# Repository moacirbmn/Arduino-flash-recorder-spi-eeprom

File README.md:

# Arduino-flash-recorder-spi-eeprom

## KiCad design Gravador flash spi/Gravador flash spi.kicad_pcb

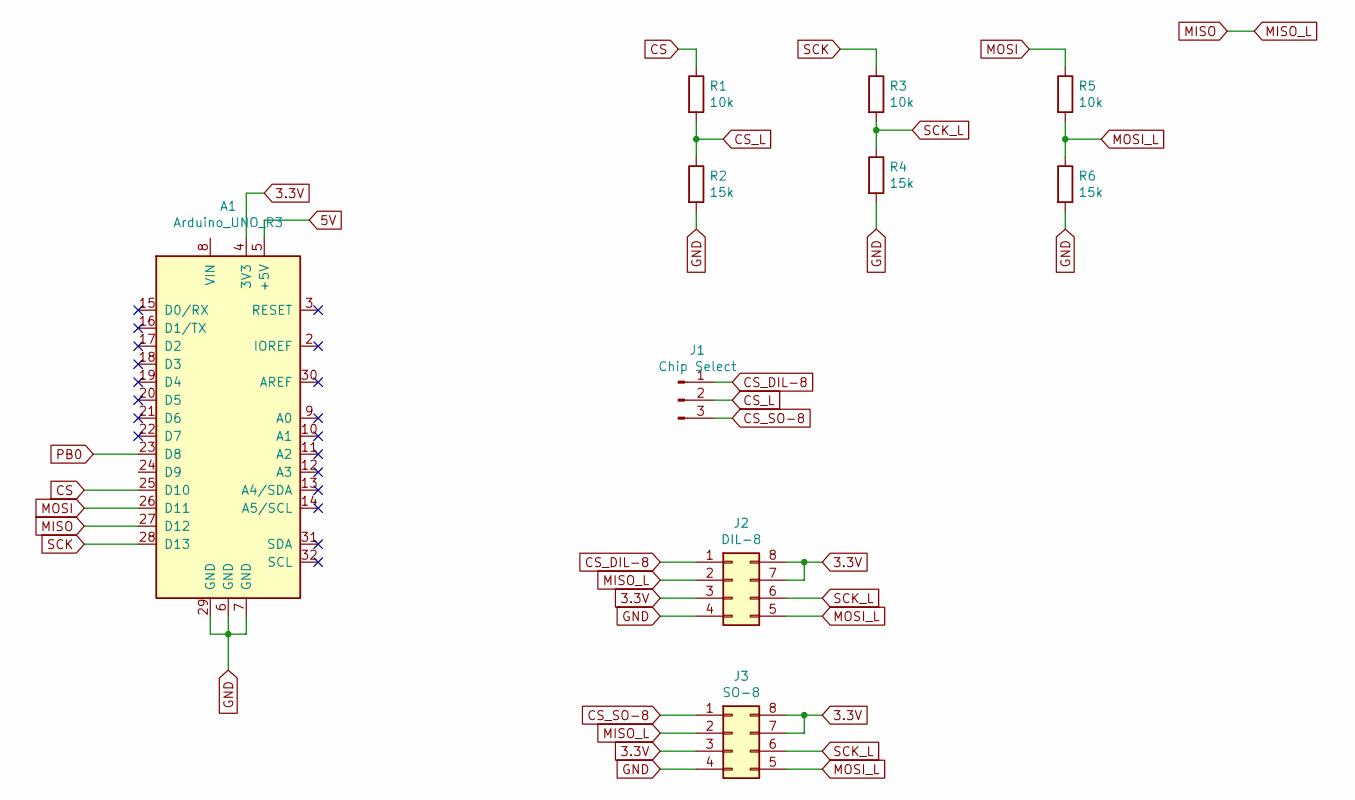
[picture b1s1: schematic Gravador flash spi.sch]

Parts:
A1: Arduino_UNO_R3; Arduino_UNO_R3_WithMountingHoles
J1: Chip Select; Pin_Header_Straight_1x03_Pitch2.54mm
J2: DIL-8; DIP-8_W7.62mm_LongPads
J3: SO-8; SO-8_5.3x6.2mm_Pitch1.27mm
R1, R3, R5: 10k; R_0805
R2, R4, R6: 15k; R_0805

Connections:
3.3V: A1.4 (3V3), J2.3, J2.7, J2.8, J3.3, J3.7, J3.8
5V: A1.5 (+5V)
CS: A1.25 (D10), R1.1
CS_DIL-8: J1.1, J2.1
CS_L: J1.2, R1.2, R2.1
CS_SO-8: J1.3, J3.1
GND: A1.6 (GND), A1.7 (GND), A1.29 (GND), J2.4, J3.4, R2.2, R4.2, R6.2
MISO: A1.27 (D12), J2.2, J3.2
MOSI: A1.26 (D11), R5.1
MOSI_L: J2.5, J3.5, R5.2, R6.1
PB0: A1.23 (D8)
SCK: A1.28 (D13), R3.1
SCK_L: J2.6, J3.6, R3.2, R4.1

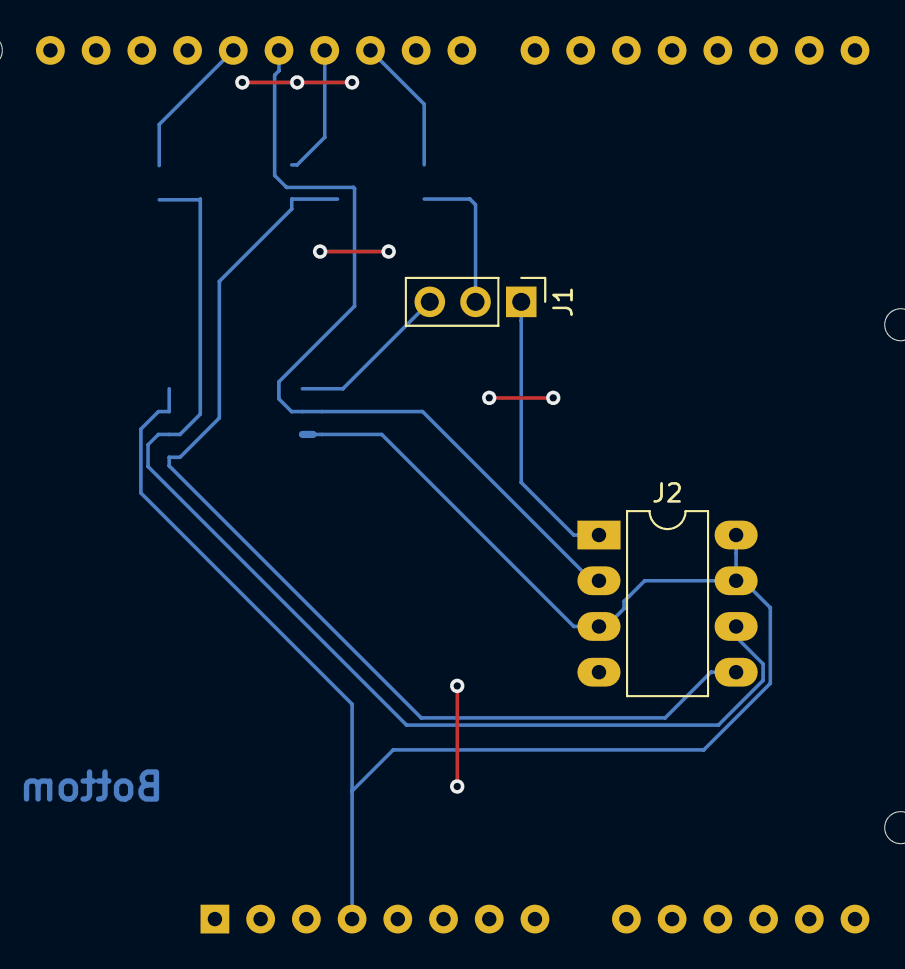
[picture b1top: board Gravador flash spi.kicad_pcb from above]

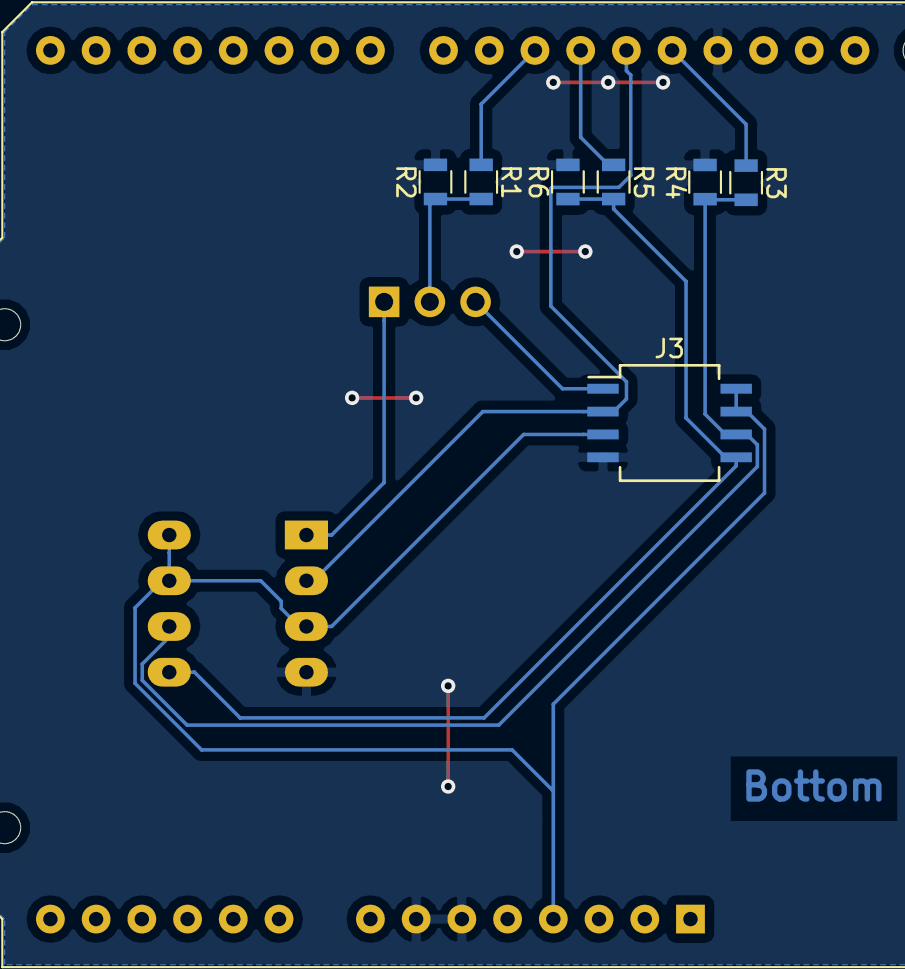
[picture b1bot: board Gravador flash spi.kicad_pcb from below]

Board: 2 copper layers, 10 parts (8 on the bottom side), 11 nets.

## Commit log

2019-01-09 esquematico e circuito pcb
2019-01-11 Corrigindo pcb
2019-01-15 adicionando jumper de aterramento
